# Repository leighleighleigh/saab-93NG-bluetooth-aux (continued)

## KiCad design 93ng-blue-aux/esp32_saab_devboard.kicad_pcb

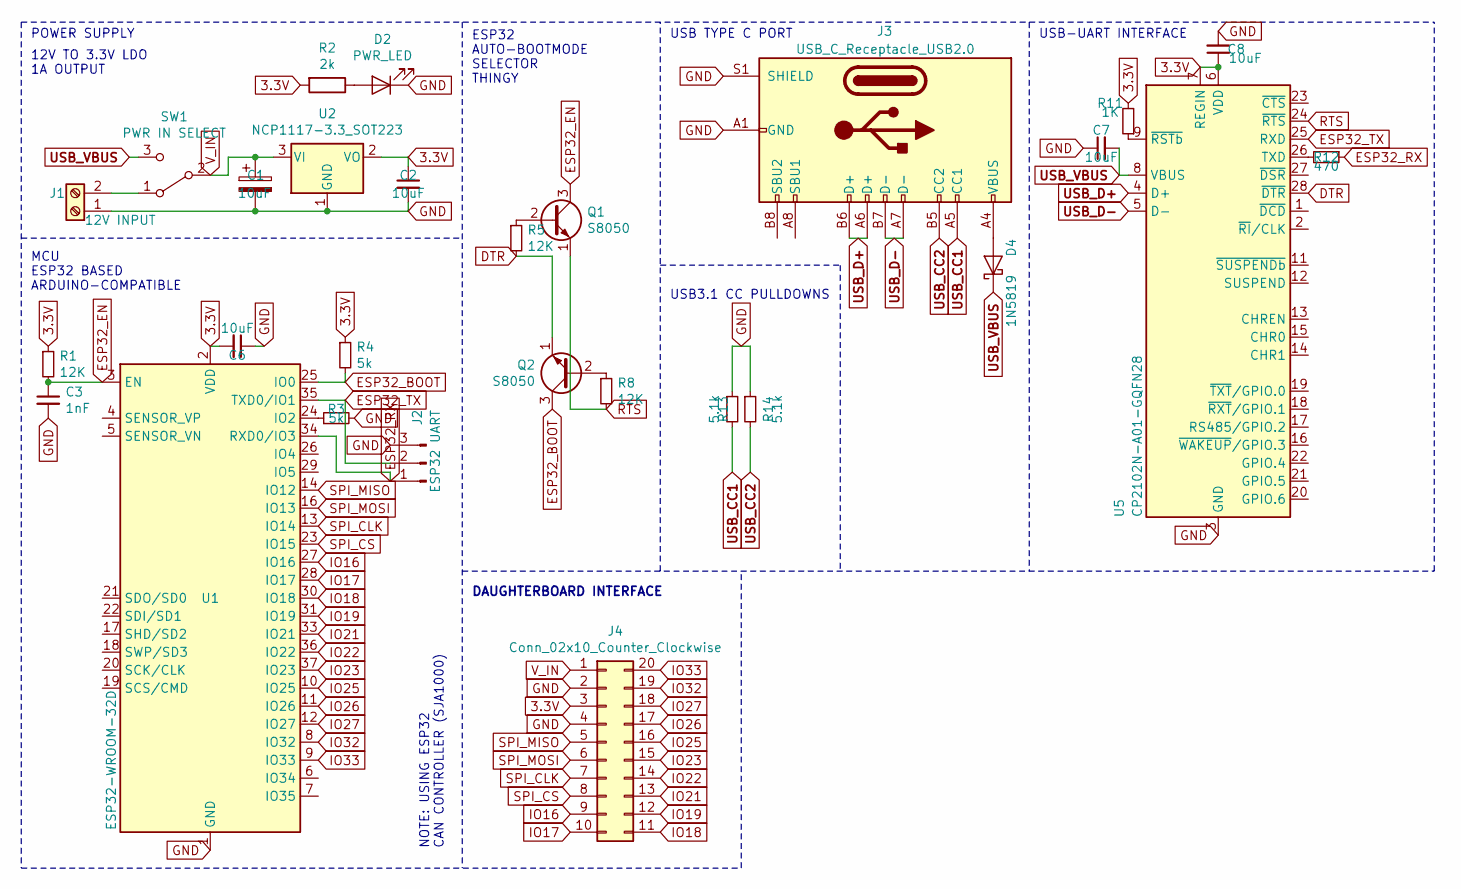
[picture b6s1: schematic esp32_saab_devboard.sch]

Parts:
C1: 10uF; C_2010_5025Metric_Pad1.52x2.65mm_HandSolder
C2, C6, C7, C8: 10uF; C_0805_2012Metric_Pad1.15x1.40mm_HandSolder
C3: 1nF; C_0805_2012Metric_Pad1.15x1.40mm_HandSolder
D2: PWR_LED; LED_0805_2012Metric_Pad1.15x1.40mm_HandSolder
D4: 1N5819; D_0805_2012Metric_Pad1.15x1.40mm_HandSolder
J1: 12V INPUT; TerminalBlock_Phoenix_MKDS-1,5-2-5.08_1x02_P5.08mm_Horizont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
J2: ESP32 UART; PinHeader_1x03_P2.54mm_Vertical
J3: USB_C_Receptacle_USB2.0; USB_C_Receptacle_Amphenol_12401610E4-2A
J4: Conn_02x10_Counter_Clockwise; PinHeader_2x10_P2.54mm_Vertical
Q1, Q2: S8050; SOT-23_Handsoldering
R1, R5, R8: 12K; R_0805_2012Metric_Pad1.15x1.40mm_HandSolder
R2: 2k; R_0805_2012Metric_Pad1.15x1.40mm_HandSolder
R3, R4: 5k; R_0805_2012Metric_Pad1.15x1.40mm_HandSolder
R11: 1K; R_0805_2012Metric_Pad1.15x1.40mm_HandSolder
R12: 470; R_0805_2012Metric_Pad1.15x1.40mm_HandSolder
R13, R14: 5.1k; R_0805_2012Metric_Pad1.15x1.40mm_HandSolder
SW1: PWR IN SELECT; PinHeader_1x03_P2.54mm_Vertical
U1: ESP32-WROOM-32D; ESP32-WROOM-32
U2: NCP1117-3.3_SOT223; SOT-223-3_TabPin2
U5: CP2102N-A01-GQFN28; QFN-28-1EP_5x5mm_P0.5mm_EP3.35x3.35mm

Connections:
3.3V: C2.1, C6.2, C8.1, J4.3, R1.1, R2.2, R4.1, R11.2, U1.2 (VDD), U2.2 (VO), U5.6 (VDD), U5.7 (REGIN)
DTR: Q2.1 (E), R5.2, U5.28 (~DTR)
ESP32_BOOT: Q2.3 (C), R4.2, U1.25 (IO0)
ESP32_EN: C3.1, Q1.3 (C), R1.2, U1.3 (EN)
ESP32_RX: J2.1, R12.1, U1.34 (RXD0/IO3)
ESP32_TX: J2.2, U1.35 (TXD0/IO1), U5.25 (RXD)
GND: C1.2, C2.2, C3.2, C6.1, C7.1, C8.2, D2.1 (K), J1.1, J2.3, J3.A1 (GND), J3.A12 (GND), J3.B1 (GND), J3.B12 (GND), J3.S1 (SHIELD), J4.2, J4.4, R3.2, R13.1, R14.1, U1.1 (GND), U1.15 (GND), U1.38 (GND), U1.39 (GND), U2.1 (GND), U5.3 (GND), U5.29 (GND)
IO16: J4.9, U1.27 (IO16)
IO17: J4.10, U1.28 (IO17)
IO18: J4.11, U1.30 (IO18)
IO19: J4.12, U1.31 (IO19)
IO21: J4.13, U1.33 (IO21)
IO22: J4.14, U1.36 (IO22)
IO23: J4.15, U1.37 (IO23)
IO25: J4.16, U1.10 (IO25)
IO26: J4.17, U1.11 (IO26)
IO27: J4.18, U1.12 (IO27)
IO32: J4.19, U1.8 (IO32)
IO33: J4.20, U1.9 (IO33)
unnamed: D2.2 (A), R2.1
unnamed: D4.2 (A), J3.A4 (VBUS), J3.A9 (VBUS), J3.B4 (VBUS), J3.B9 (VBUS)
unnamed: J1.2, SW1.1 (A)
unnamed: Q1.2 (B), R5.1
unnamed: Q2.2 (B), R8.1
unnamed: R3.1, U1.24 (IO2)
unnamed: R11.1, U5.9 (~RSTb)
unnamed: R12.2, U5.26 (TXD)
RTS: Q1.1 (E), R8.2, U5.24 (~RTS)
SPI_CLK: J4.7, U1.13 (IO14)
SPI_CS: J4.8, U1.23 (IO15)
SPI_MISO: J4.5, U1.14 (IO12)
SPI_MOSI: J4.6, U1.16 (IO13)
USB_CC1: J3.A5 (CC1), R13.2
USB_CC2: J3.B5 (CC2), R14.2
USB_D+: J3.A6 (D+), J3.B6 (D+), U5.4 (D+)
USB_D-: J3.A7 (D-), J3.B7 (D-), U5.5 (D-)
USB_VBUS: C7.2, D4.1 (K), SW1.3 (C), U5.8 (VBUS)
V_IN: C1.1, J4.1, SW1.2 (B), U2.3 (VI)

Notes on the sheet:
POWER SUPPLY
12V TO 3.3V LDO 1A OUTPUT
MCU ESP32 BASED ARDUINO-COMPATIBLE
NOTE: USING ESP32 CAN CONTROLLER (SJA1000)
USB3.1 CC PULLDOWNS
USB TYPE C PORT
USB-UART INTERFACE
ESP32 AUTO-BOOTMODE SELECTOR THINGY
DAUGHTERBOARD INTERFACE

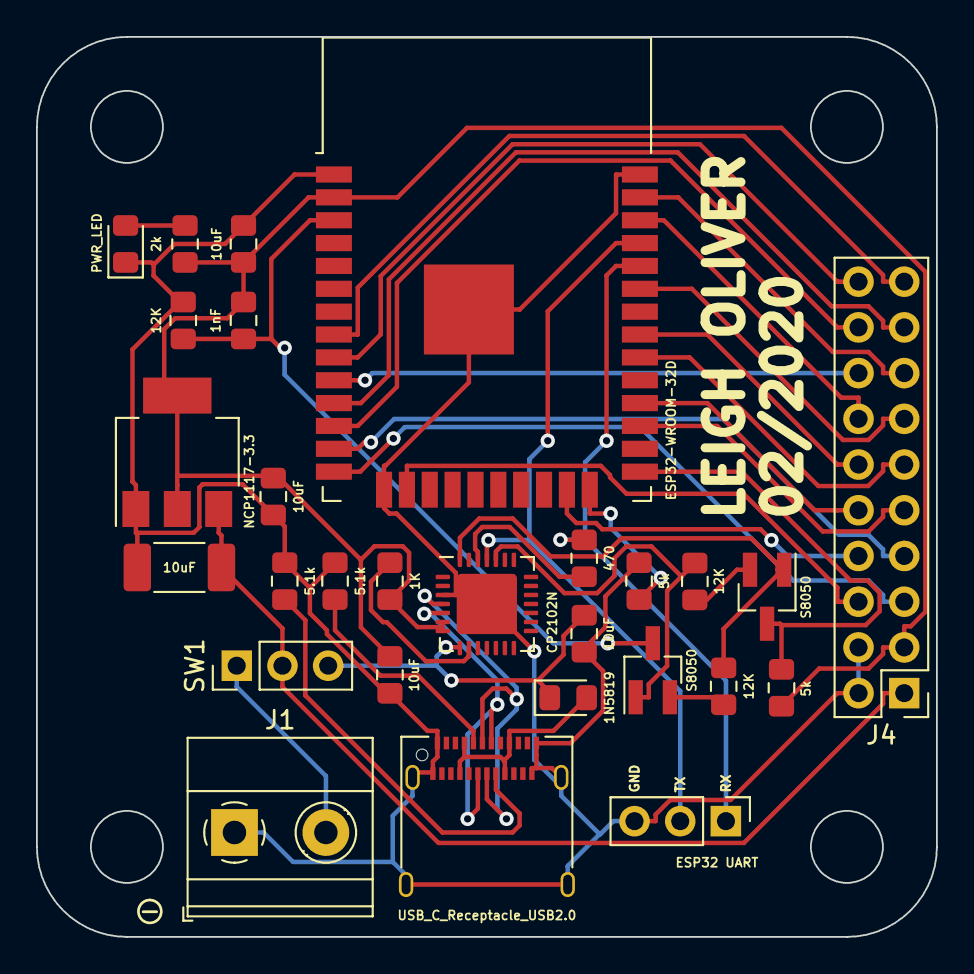
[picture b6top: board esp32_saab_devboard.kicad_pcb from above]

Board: 2 copper layers, 50.0 x 50.0 mm, 28 parts (0 on the bottom side), 38 nets.

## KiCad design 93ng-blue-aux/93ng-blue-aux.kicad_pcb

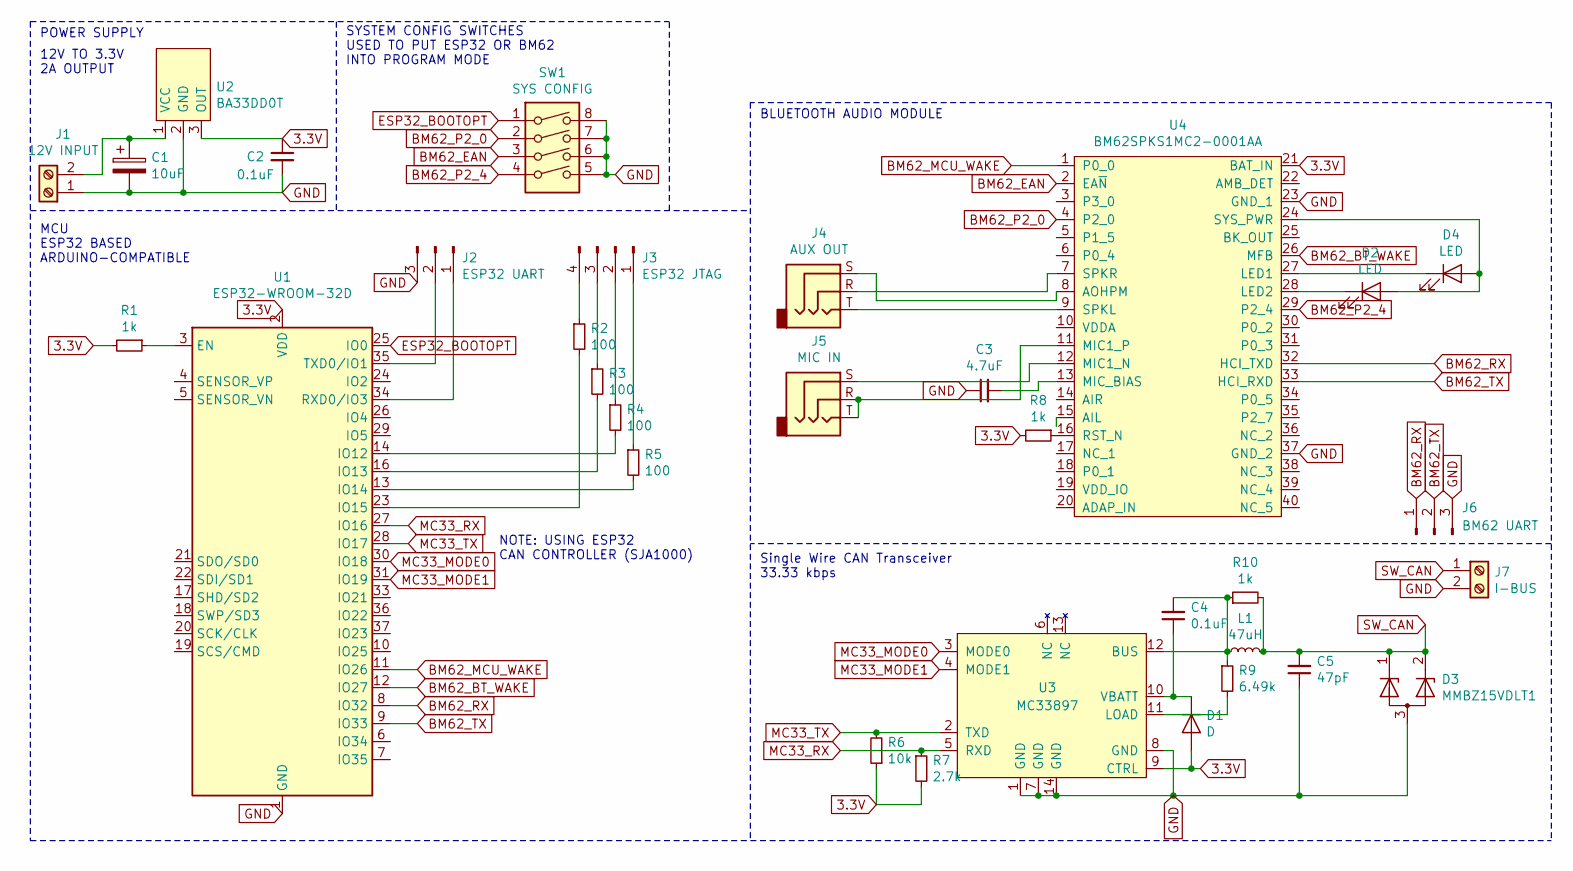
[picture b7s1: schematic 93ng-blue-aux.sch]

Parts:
C1: 10uF; CP_Radial_D10.0mm_P5.00mm
C2, C4: 0.1uF; C_0805_2012Metric_Pad1.15x1.40mm_HandSolder
C3: 4.7uF; C_0805_2012Metric_Pad1.15x1.40mm_HandSolder
C5: 47pF; C_0805_2012Metric_Pad1.15x1.40mm_HandSolder
D1: D; D_0805_2012Metric_Pad1.15x1.40mm_HandSolder
D2, D4: LED; LED_0805_2012Metric_Pad1.15x1.40mm_HandSolder
D3: MMBZ15VDLT1; SOT-23
J1: 12V INPUT; TerminalBlock_Phoenix_MKDS-3-2-5.08_1x02_P5.08mm_Horizontal
J2: ESP32 UART; PinHeader_1x03_P2.54mm_Vertical
J3: ESP32 JTAG; PinHeader_1x04_P2.54mm_Vertical
J4: AUX OUT; Jack_3.5mm_CUI_SJ-3523-SMT_Horizontal
J5: MIC IN; Jack_3.5mm_CUI_SJ-3523-SMT_Horizontal
J6: BM62 UART; PinHeader_1x03_P2.54mm_Vertical
J7: I-BUS; TerminalBlock_Phoenix_MKDS-3-2-5.08_1x02_P5.08mm_Horizontal
L1: 47uH; L_0805_2012Metric_Pad1.15x1.40mm_HandSolder
R1, R8, R10: 1k; R_0805_2012Metric_Pad1.15x1.40mm_HandSolder
R2, R3, R4, R5: 100; R_0805_2012Metric_Pad1.15x1.40mm_HandSolder
R6: 10k; R_0805_2012Metric_Pad1.15x1.40mm_HandSolder
R7: 2.7k; R_0805_2012Metric_Pad1.15x1.40mm_HandSolder
R9: 6.49k; R_0805_2012Metric_Pad1.15x1.40mm_HandSolder
SW1: SYS CONFIG; SW_DIP_SPSTx04_Slide_Omron_A6S-410x_W8.9mm_P2.54mm
U1: ESP32-WROOM-32D; ESP32-WROOM-32
U2: BA33DD0T; TO-220-3_Vertical
U3: MC33897; SOIC-14_3.9x8.7mm_P1.27mm
U4: BM62SPKS1MC2-0001AA

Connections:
3.3V: C2.1, D1.2 (A), R1.2, R6.1, R7.2, R8.2, U1.2 (VDD), U2.3 (OUT), U3.9 (CTRL), U4.21 (BAT_IN)
BM62_BT_WAKE: U1.12 (IO27), U4.26 (MFB)
BM62_EAN: SW1.3, U4.2 (EA~N)
BM62_MCU_WAKE: U1.11 (IO26), U4.1 (P0_0)
BM62_P2_0: SW1.2, U4.4 (P2_0)
BM62_P2_4: SW1.4, U4.29 (P2_4)
BM62_RX: J6.1, U1.8 (IO32), U4.32 (HCI_TXD)
BM62_TX: J6.2, U1.9 (IO33), U4.33 (HCI_RXD)
ESP32_BOOTOPT: SW1.1, U1.25 (IO0)
GND: C1.2, C2.2, C3.1, C5.1, D3.3 (A), J1.1, J2.3, J6.3, J7.2, SW1.5, SW1.6, SW1.7, SW1.8, U1.1 (GND), U1.15 (GND), U1.38 (GND), U1.39 (GND), U2.2 (GND), U3.1 (GND), U3.7 (GND), U3.8 (GND), U3.14 (GND), U4.23 (GND_1), U4.37 (GND_2)
MC33_MODE0: U1.30 (IO18), U3.3 (MODE0)
MC33_MODE1: U1.31 (IO19), U3.4 (MODE1)
MC33_RX: R7.1, U1.27 (IO16), U3.5 (RXD)
MC33_TX: R6.2, U1.28 (IO17), U3.2 (TXD)
unnamed: C1.1, J1.2, U2.1 (VCC)
unnamed: C3.2, U4.13 (MIC_BIAS)
unnamed: C4.1, D1.1 (K), U3.10 (VBATT)
unnamed: C4.2, L1.1, R9.1, R10.1, U3.12 (BUS)
unnamed: D2.1 (K), U4.28 (LED2)
unnamed: D2.2 (A), D4.2 (A), U4.24 (SYS_PWR)
unnamed: D4.1 (K), U4.27 (LED1)
unnamed: J2.1, U1.34 (RXD0/IO3)
unnamed: J2.2, U1.35 (TXD0/IO1)
unnamed: J3.1, R5.1
unnamed: J3.2, R4.1
unnamed: J3.3, R3.1
unnamed: J3.4, R2.1
unnamed: J4.R, U4.7 (SPKR)
unnamed: J4.S, U4.8 (AOHPM)
unnamed: J4.T, U4.9 (SPKL)
unnamed: J5.R, J5.T, U4.11 (MIC1_P)
unnamed: J5.S, U4.12 (MIC1_N)
unnamed: R1.1, U1.3 (EN)
unnamed: R2.2, U1.23 (IO15)
unnamed: R3.2, U1.16 (IO13)
unnamed: R4.2, U1.14 (IO12)
unnamed: R5.2, U1.13 (IO14)
unnamed: R8.1, U4.16 (RST_N)
unnamed: R9.2, U3.11 (LOAD)
SW_CAN: C5.2, D3.1 (K), D3.2 (K), J7.1, L1.2, R10.2

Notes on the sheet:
POWER SUPPLY
12V TO 3.3V 2A OUTPUT
MCU ESP32 BASED ARDUINO-COMPATIBLE
NOTE: USING ESP32 CAN CONTROLLER (SJA1000)
Single Wire CAN Transceiver 33.33 kbps
BLUETOOTH AUDIO MODULE
SYSTEM CONFIG SWITCHES USED TO PUT ESP32 OR BM62 INTO PROGRAM MODE

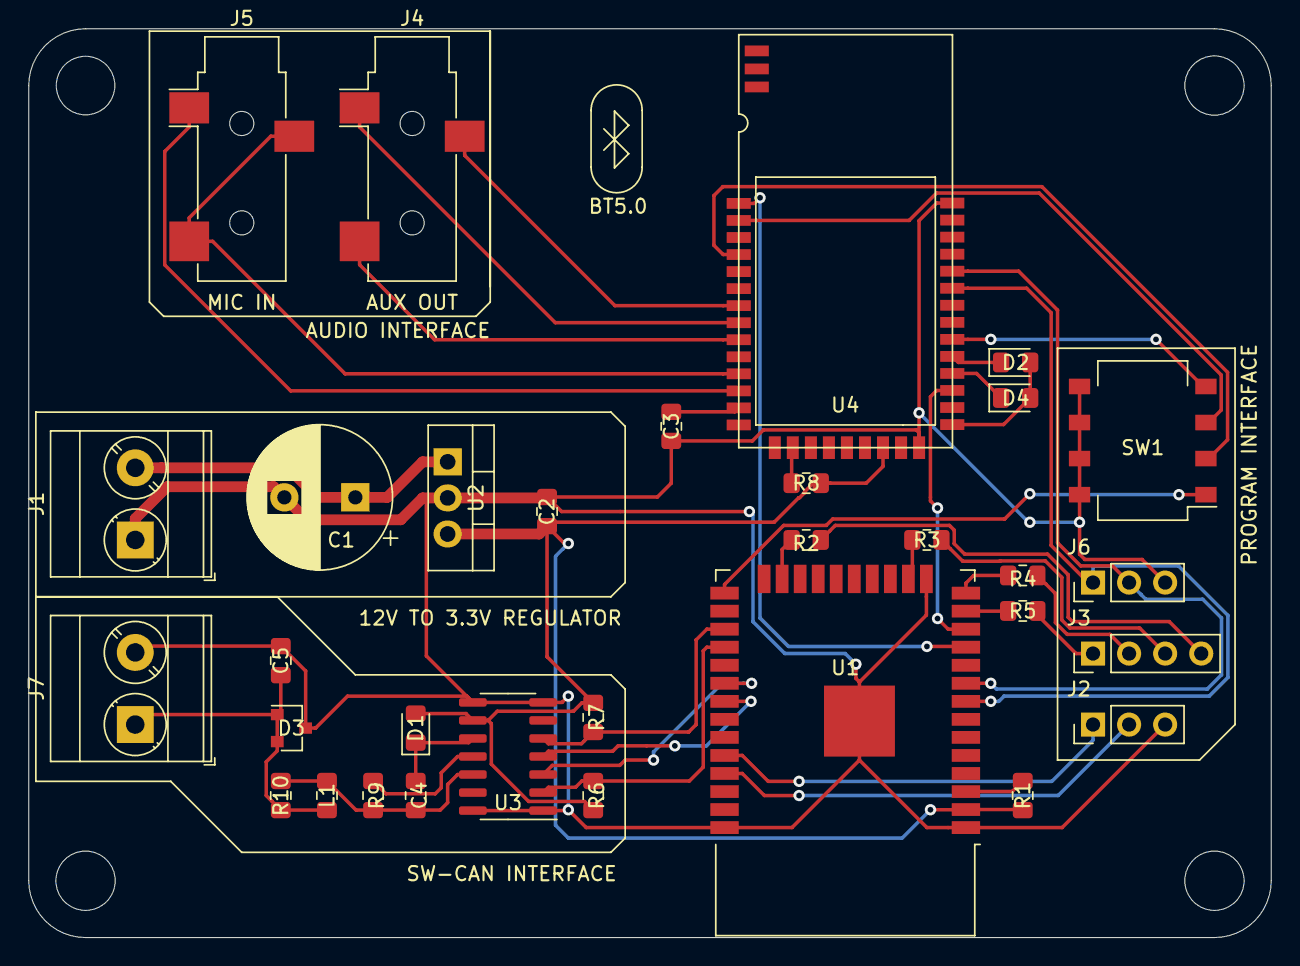
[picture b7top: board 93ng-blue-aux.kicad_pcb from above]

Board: 2 copper layers, 87.5 x 64.0 mm, 32 parts (0 on the bottom side), 40 nets.

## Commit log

2020-02-04 Added symbol files for all major components. Added footprint for CAN interface.
2020-02-05 Finished first draft of schematic. Made symbol for new LDO
2020-02-05 More work on schematic, focus on debugging utility, and started layout of PCB. Made footprint for BM62.
2020-02-05 Added picture of schematic. Added some screw terminals.
2020-02-09 Completed roughest PCB layout ever
2020-02-19 Added 12V input filter cap
2020-02-19 Working on 100mmx100mm board design. Adjusted input power filter cap size. Re-designed bluetooth antenna keepout comment, and added courtyard to module.
2020-02-21 PCB Layout progress.
2020-02-22 Finished trace layout.
2020-02-22 Added ESP32 only schematic, with intention to add USB-C serial interface.
2020-02-23 More work on standalone ESP32 module
2020-02-23 Playing with 50x50mm layout
2020-02-24 Placed all the components roughly! Added ground plane!
2020-02-24 Did routing. Decided it looks horrible. Need to investigate better USB-C solution, remove the PD chip.
2020-02-25 Made new version without USBC-PD chip, and simple pulldowns. Placement looks good.
2020-02-25 Automatic freerouting job. Plot export
2020-02-26 Updated the input power select to be an actual switch, allowing easier access if in a stacked configuration.
2020-02-26 Working on saab board interconnect
2020-02-26 I forget what I did.
2020-02-26 Completed first draft of final ESP32 board design, with autorouting
2020-02-26 Switched to low-profile phoenix
2020-02-27 Adjusted pcb text
2020-02-27 Added plot output files
2020-03-06 Removed old projects and boards
2020-04-14 Added BT music and CAN bus code
2020-04-19 A2DP SAAB Receiver Prototype Works!
2020-04-22 Updated README.md with issues
2020-04-26 Experimenting with ICM2 display output for bluetooth media state, looks cool so far, unsure how it will be implemented with the stock system however.
2020-04-26 Working on simple module board, to upgrade from current breadboard solution
2020-04-26 Updates to revert back to non-display use
2020-05-01 Updated to handle weird disconnects/reconnects gracefully
2020-05-01 Improved streaming performance by modifying I2C config
2020-05-01 Allowed for AVCRP testing, but no google assistant. Probs in HFP...
2020-05-06 Made simple PCB
2020-05-08 Updated PCB text
2020-05-08 Updated CAN connector pads
2020-05-13 Sent off first prototype board to the fab house
2020-05-21 Fixed CC3 DC-DC module footprint orientation. It was flipped. Tied enable pin to gnd. Re-routed I2C data.
2020-05-31 Update README.md with first prototype image.
2020-06-02 Working on more tightly integrated esp32-based bluetooth board
2020-06-15 Working on new bluetooth+can module from scratch
2020-06-17 Experimenting with newer DAC chips
2020-08-11 Working on new simplified audio module
2020-08-16 Working on V3 based on sid-re-board
2020-08-20 Random audio stuff
2020-10-31 Attempt EEPROM storage of last connected addr
2020-11-02 Figured out debug mode in PIO, reconnect code almost working
2020-11-02 EEPROM Auto re-connect working
2021-01-26 Trying to add assistant
2021-02-11 Updated code for more reliable AHCDP or whatever connectino
2021-02-11 Code
2021-02-27 Attempt at voice assistant trigger and A2DP/HPF coexistance
2021-02-28 Remapped voice to voice button
2021-05-09 Cleaned up repo
2021-05-30 Downgraded ESP-IDF platform
2021-09-01 Switch to pschatzmann's ESP32-A2DP library, use Github lib_deps
    -Use more up-to-date A2DP library by pschatzmann.
    -Fix up main.cpp to support this new library.
    -Include Github libraries to platformio.ini lib_deps to stay up-to-date.
    -General fixes and cleanup.
    -
    No noise or distortion was found using this code and UDA1334A on a Saab 9-3 AUX input, even at max Bluetooth volume.
2021-09-16 Fix voice assistant support, add the ability to answer phone calls
    Not tested in the car yet, so not sure if I have mapped the steering buttons right.
2021-12-12 Switch to the latest ESP32 Arduino 2.0.1 based on ESP-IDF 4.4 and arduino-upstream development ESP32 platform branch
2021-12-12 Use LSB I2S format
    According to the UDA1334A datasheet, the chip uses LSB format I2S.
    With this I did notice distortion on high volume settings while testing using headphones, but it might be fine on the Saab Aux.
2021-12-12 Swap LR channels, enable auto-connect, other minor changes
2021-12-13 Auto-reconnect issue workaround
    See this for details: https://github.com/pschatzmann/ESP32-A2DP/issues/97#issuecomment-992484405
2021-12-14 Revert Auto-reconnect issue workaround
    This has been fixed in the ESP32-A2DP library: https://github.com/pschatzmann/ESP32-A2DP/commit/ccfe7199bd7e32f33e90e9d81b04a3b1a034fb6f
2021-12-14 Switch to MSB I2S
    Since SFOR1 and SFOR0 are connected to GND, UDA1334A is in I2S-bus input format (MSB)
    Have to thank Espressif for the excellent i2s_comm_format_t documentation: https://docs.espressif.com/projects/esp-idf/en/latest/esp32/api-reference/peripherals/i2s.html#_CPPv417i2s_comm_format_t
    I2S_COMM_FORMAT_STAND_MSB is I2S format LSB, and I2S_COMM_FORMAT_STAND_I2S is I2S format MSB
2021-12-14 Add set_auto_reconnect parameters
2021-12-19 Remove WiFi code
    It is not necessary to set the WiFi mode to null to disable it. It is enough to just not include esp_wifi.h and not call any WiFi code.
    This also frees up a decent chunk of RAM and Flash.
2021-12-19 Fix BT HFP callback logging
    If debug level is increased in platformio.ini, this will show BT HFP logging in the serial console.
    This will be helpful in figuring out how to reject a call with the steering wheel button when a call is in progress.
2021-12-19 More info for build notes in the readme
2021-12-19 Remove rtc_clock_apll_enable line
    This seems to have been fixed ages ago in ESP-IDF:
    https://github.com/espressif/esp-idf/pull/3648
    https://github.com/espressif/esp-idf/issues/3380
2021-12-19 Start playing audio immediately after connecting/reconnecting to phone
2022-01-11 Found working specs for PCM5102
2022-01-15 Added .gitignore for build folders
2022-01-15 a2dp example compiles
2022-07-15 Crazy-hacky, but working, CANelloni protocol fork
2022-08-07 Repo cleanup 2022. Added WIP hardware files for V2 of the PCB
    Commit squash
2022-08-10 Added top and bottom faceplates. Improved silkscreen labels for pinouts, buttons, connectors.
2022-08-11 Adjusted silkscreen labels to reduce clutter. Added GPIO header for external buttons or LEDs. Added second PCB faceplate, for the bottom-side of the assembly.
2022-08-17 Updated silkscreen
2022-08-25 Added new CP2102 footprint from real-world measurements
2022-09-22 Started working on module-based V2 PCB, which is easier to build.
2022-09-22 V2 Kit looking good!
2022-09-24 Added bonus power header, which can be used to support additional add-ons in the future
2022-09-30 Updated README with hw_kit_v2.png
2022-09-30 Added 3D model to Molex connector
2022-09-30 Added enclosure 3D model... it doesnt fit oops
2022-10-07 Added PIO environment for Lolin32Lite, tested initial build without MCP2515 CAN
